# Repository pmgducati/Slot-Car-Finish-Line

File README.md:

# Slot Car Finish Line
 Pole Position Tower and Finsh line for Artin Slot Car Race Track

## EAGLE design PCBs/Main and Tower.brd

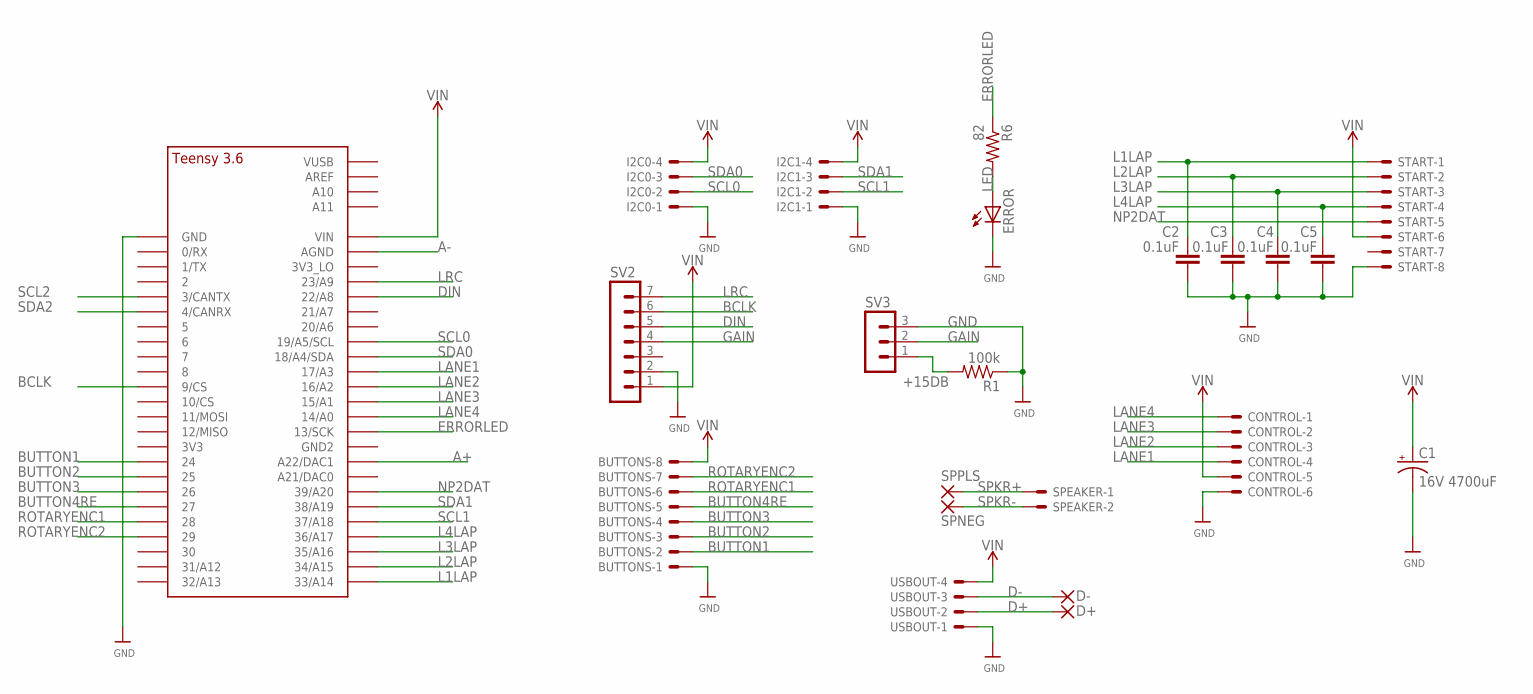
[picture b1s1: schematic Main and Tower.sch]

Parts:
BUTTONS: KK-156-8
C1: 16V 4700uF; CAPPRD550W110D1250H2500B
C2, C3, C4, C5: 0.1uF; CAPC3216X135
CONTROL: KK-156-6
D+: 1,6/0,8
D-: 1,6/0,8
ERROR: LEDCHIPLED_1206; CHIPLED_1206
I2C0, I2C1: KK-156-4
R1: 100k; M1206
R6: 82; M1206
SPEAKER: KK-156-2
SPNEG: 2,54/1,1
SPPLS: 2,54/1,1
START: KK-156-8
SV2: MA07-1
SV3: MA03-1
U$1: TEENSY_3.5/3.6_BASIC
USBOUT: KK-156-4

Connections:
+15DB: R1.2, SV3.1
A+: U$1.A22/DAC1
A-: U$1.AGND
BCLK: SV2.6, U$1.9/CS
BUTTON1: BUTTONS.2, U$1.24
BUTTON2: BUTTONS.3, U$1.25
BUTTON3: BUTTONS.4, U$1.26
BUTTON4RE: BUTTONS.5, U$1.27
D+: D+.1, USBOUT.2
D-: D-.1, USBOUT.3
DIN: SV2.5, U$1.22/A8
ERRORLED: R6.1, U$1.13/SCK
GAIN: SV2.4, SV3.2
GND: BUTTONS.1, C1.2 (-), C2.2, C3.2, C4.2, C5.2, CONTROL.6, ERROR.C, I2C0.1, I2C1.1, R1.1, START.8, SV2.2, SV3.3, U$1.GND, USBOUT.1
L1LAP: C2.1, START.1, U$1.33/A14
L2LAP: C3.1, START.2, U$1.34/A15
L3LAP: C4.1, START.3, U$1.35/A16
L4LAP: C5.1, START.4, U$1.36/A17
LANE1: CONTROL.4, U$1.17/A3
LANE2: CONTROL.3, U$1.16/A2
LANE3: CONTROL.2, U$1.15/A1
LANE4: CONTROL.1, U$1.14/A0
LED: ERROR.A, R6.2
LRC: SV2.7, U$1.23/A9
NP2DAT: START.5, U$1.39/A20
ROTARYENC1: BUTTONS.6, U$1.28
ROTARYENC2: BUTTONS.7, U$1.29
SCL0: I2C0.2, U$1.19/A5/SCL
SCL1: I2C1.2, U$1.37/A18
SCL2: U$1.3/CANTX
SDA0: I2C0.3, U$1.18/A4/SDA
SDA1: I2C1.3, U$1.38/A19
SDA2: U$1.4/CANRX
SPKR+: SPEAKER.1, SPPLS.1
SPKR-: SPEAKER.2, SPNEG.1
VIN: BUTTONS.8, C1.1 (+), CONTROL.5, I2C0.4, I2C1.4, START.6, SV2.1, U$1.VIN, USBOUT.4

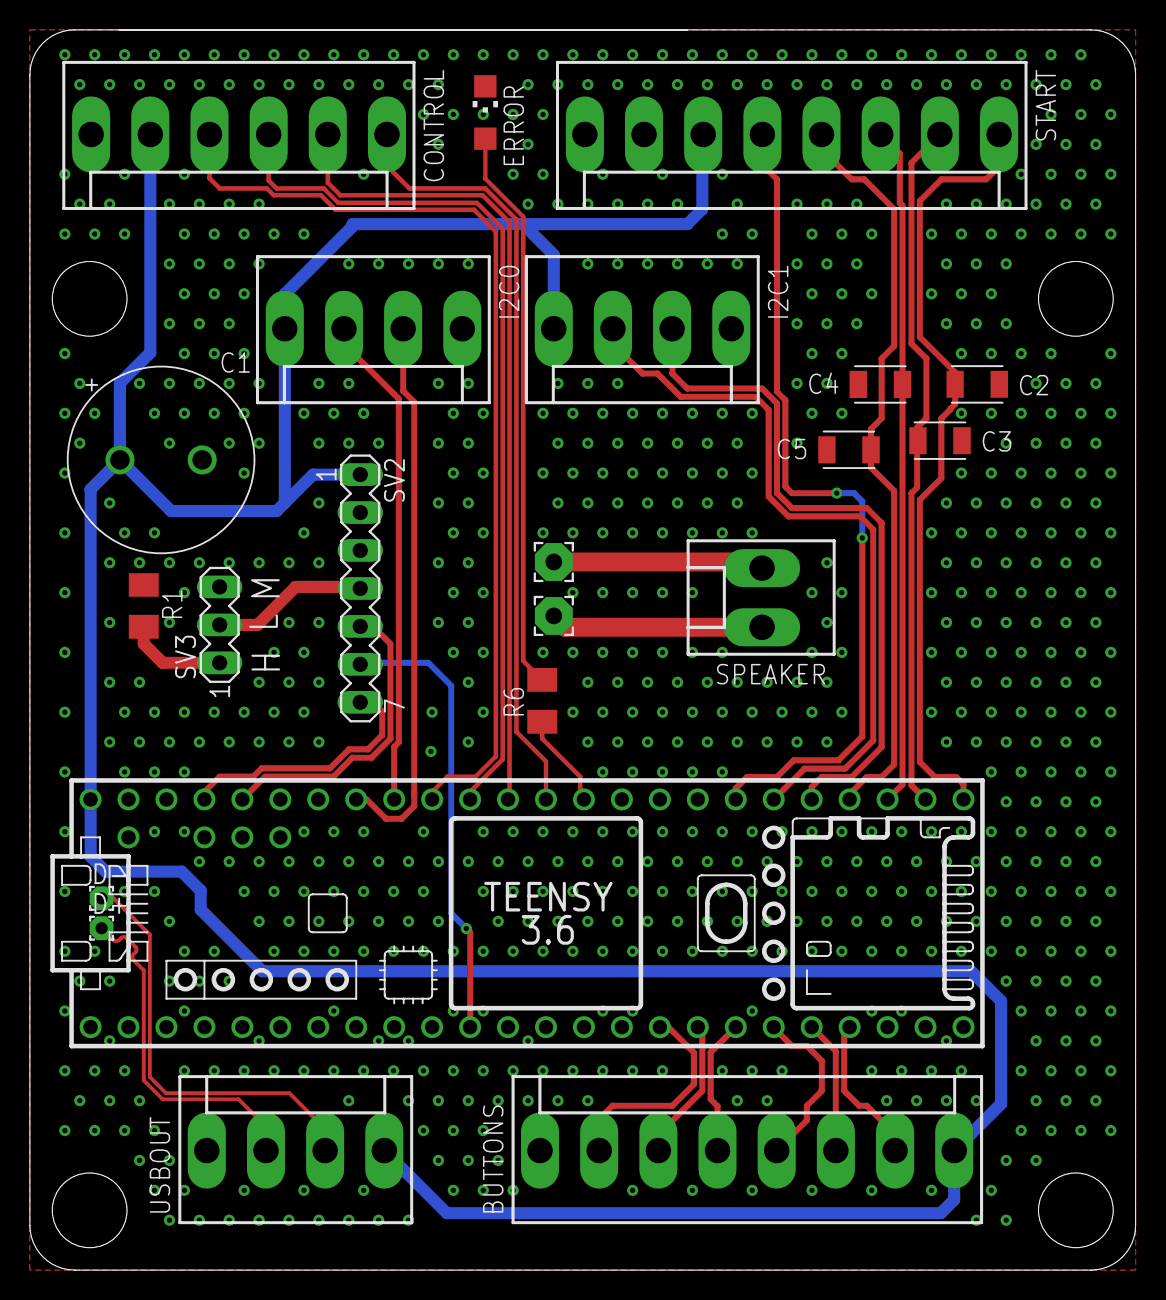
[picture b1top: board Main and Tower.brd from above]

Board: 2 copper layers, 74.0 x 83.0 mm, 22 parts (0 on the bottom side), 32 nets.

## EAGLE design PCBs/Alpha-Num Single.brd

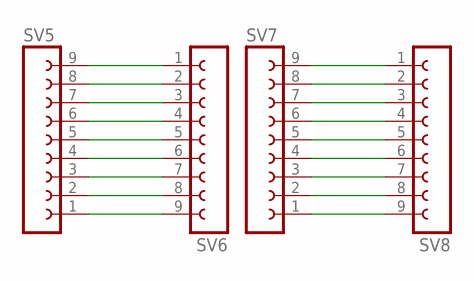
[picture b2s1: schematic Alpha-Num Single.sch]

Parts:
SV5, SV6, SV7, SV8: FE09-1; FE09

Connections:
unnamed: SV5.9, SV6.1
unnamed: SV5.8, SV6.2
unnamed: SV5.7, SV6.3
unnamed: SV5.6, SV6.4
unnamed: SV5.5, SV6.5
unnamed: SV5.4, SV6.6
unnamed: SV5.3, SV6.7
unnamed: SV5.2, SV6.8
unnamed: SV5.1, SV6.9
unnamed: SV7.9, SV8.1
unnamed: SV7.8, SV8.2
unnamed: SV7.7, SV8.3
unnamed: SV7.6, SV8.4
unnamed: SV7.5, SV8.5
unnamed: SV7.4, SV8.6
unnamed: SV7.3, SV8.7
unnamed: SV7.2, SV8.8
unnamed: SV7.1, SV8.9

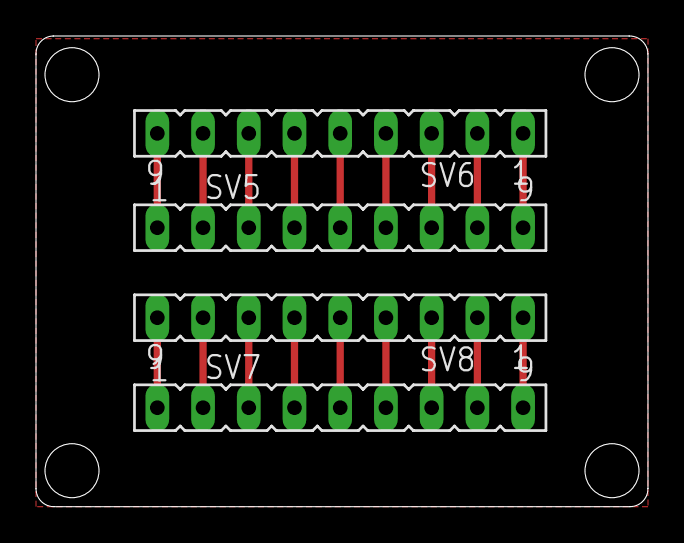
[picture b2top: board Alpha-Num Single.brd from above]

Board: 2 copper layers, 34.0 x 26.1 mm, 4 parts (0 on the bottom side), 18 nets.

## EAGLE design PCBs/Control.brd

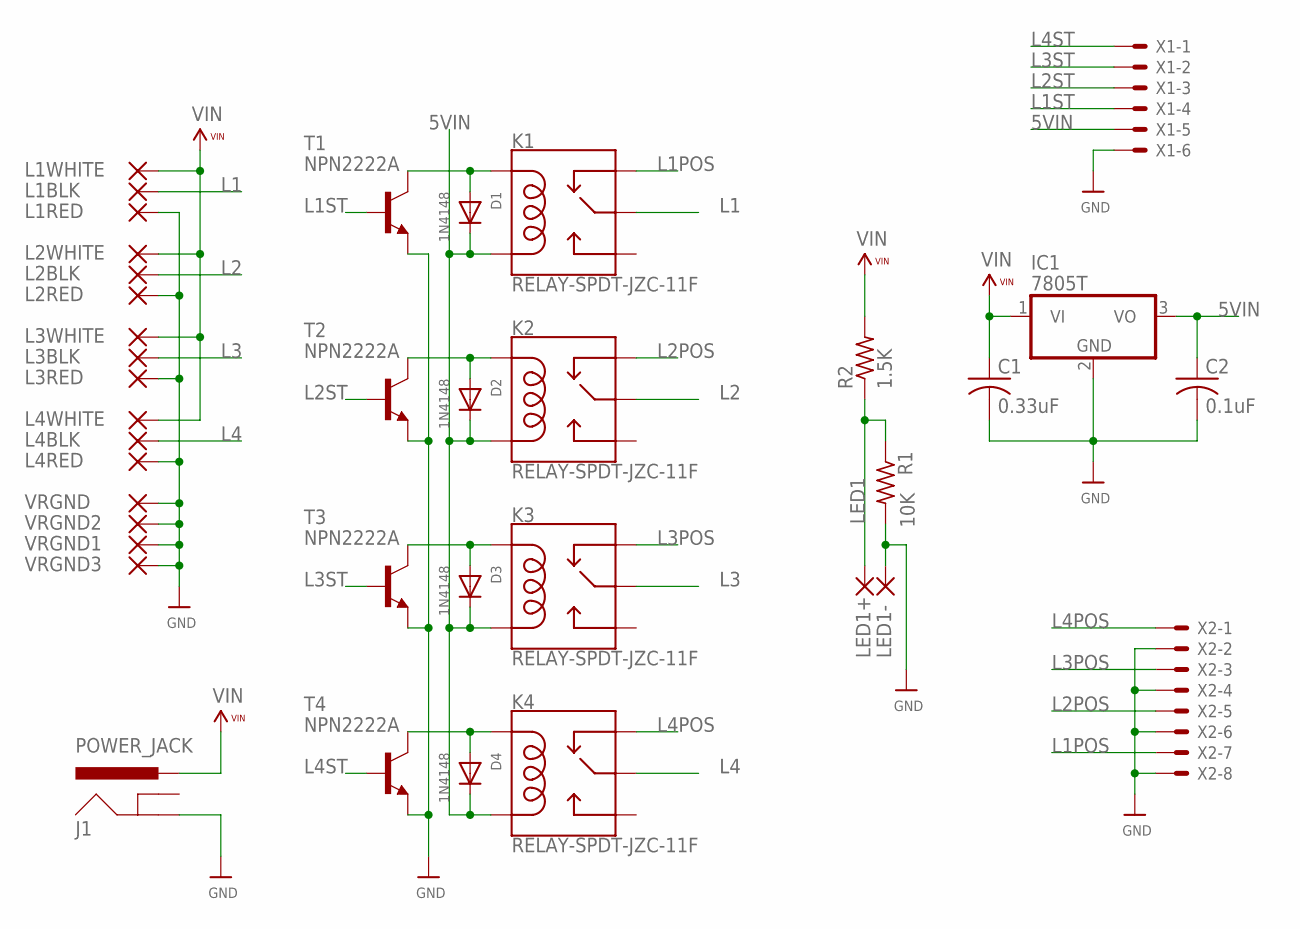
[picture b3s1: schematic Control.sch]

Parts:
C1: 0.33uF; C1206
C2: 0.1uF; C1206
D1, D2, D3, D4: 1N4148; DO-1N4148
IC1: 7805T; TO220H
J1: POWER_JACK; POWER_JACK_PTH
K1, K2, K3, K4: RELAY-SPDT-JZC-11F; RELAY-JZC
L1BLK, L1RED, L1WHITE, L2BLK, L2RED, L2WHITE, L3BLK, L3RED, L3WHITE, L4BLK, L4RED, L4WHITE: SMD5; SMD5,5X5
LED1+, LED1-: SMD5; SMD2,54-5,08
R1: 10K; M1206
R2: 1.5K; M1206
T1, T2, T3, T4: NPN2222A; TO92
VRGND, VRGND1, VRGND2, VRGND3: SMD5; SMD5,5X5
X1: KK-156-6
X2: KK-156-8

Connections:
5VIN: C2.1, D1.C, D2.C, D3.C, D4.C, IC1.3 (VO), K1.1 (COIL2), K2.1 (COIL2), K3.1 (COIL2), K4.1 (COIL2), X1.5
GND: C1.2, C2.2, IC1.2 (GND), J1.GND, L1RED.1, L2RED.1, L3RED.1, L4RED.1, LED1-.1, R1.2, T1.3 (E), T2.3 (E), T3.3 (E), T4.3 (E), VRGND.1, VRGND1.1, VRGND2.1, VRGND3.1, X1.6, X2.2, X2.4, X2.6, X2.8
L1: K1.4 (MAIN), L1BLK.1
L1POS: K1.2 (NC), X2.7
L1ST: T1.2 (B), X1.4
L2: K2.4 (MAIN), L2BLK.1
L2POS: K2.2 (NC), X2.5
L2ST: T2.2 (B), X1.3
L3: K3.4 (MAIN), L3BLK.1
L3POS: K3.2 (NC), X2.3
L3ST: T3.2 (B), X1.2
L4: K4.4 (MAIN), L4BLK.1
L4POS: K4.2 (NC), X2.1
L4ST: T4.2 (B), X1.1
LED1: LED1+.1, R1.1, R2.1
unnamed: D2.A, K2.5 (COIL1), T2.1 (C)
unnamed: D1.A, K1.5 (COIL1), T1.1 (C)
unnamed: D3.A, K3.5 (COIL1), T3.1 (C)
unnamed: D4.A, K4.5 (COIL1), T4.1 (C)
VIN: C1.1, IC1.1 (VI), J1.PWR, L1WHITE.1, L2WHITE.1, L3WHITE.1, L4WHITE.1, R2.2

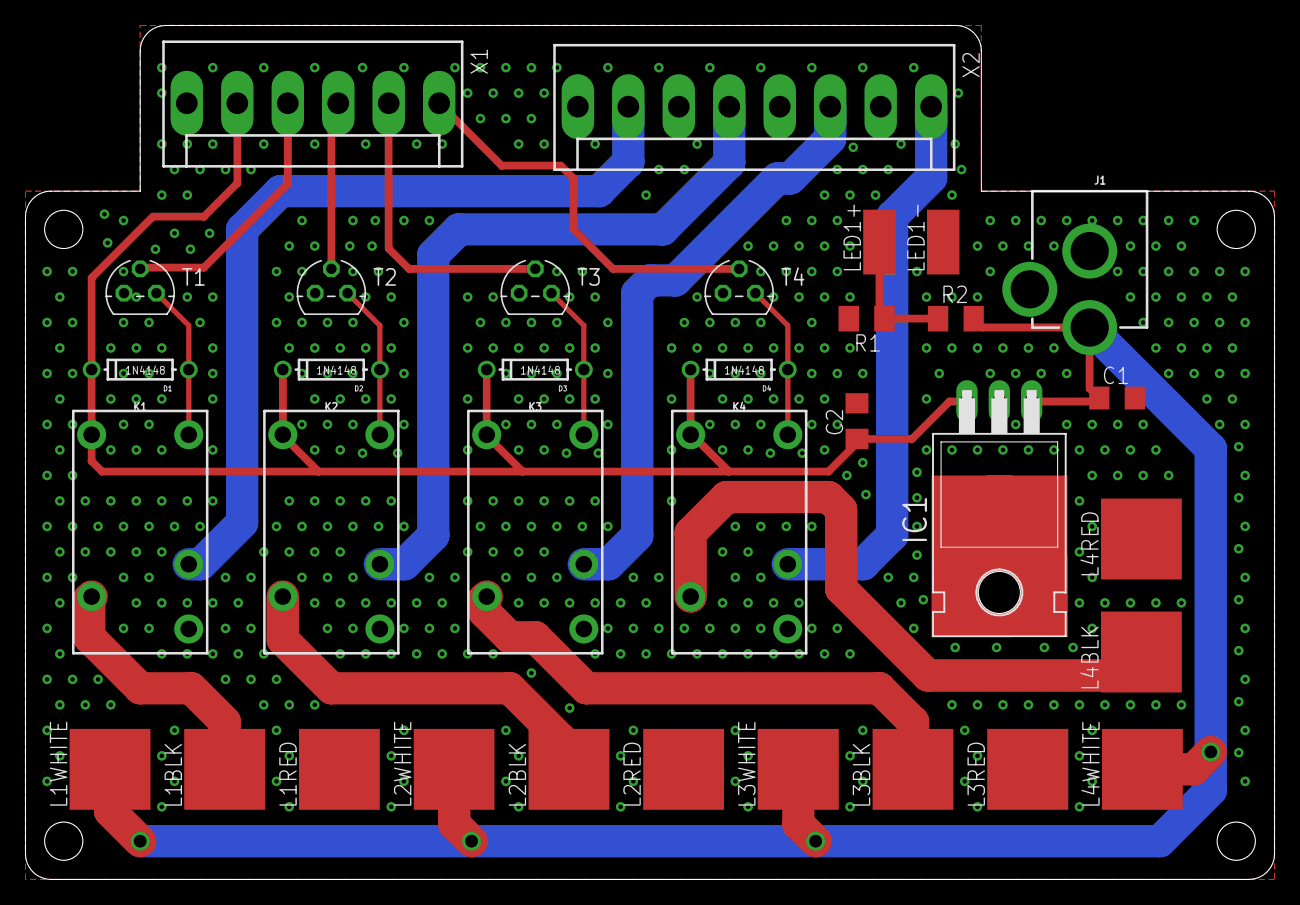
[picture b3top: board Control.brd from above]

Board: 2 copper layers, 98.0 x 67.0 mm, 38 parts (0 on the bottom side), 20 nets.

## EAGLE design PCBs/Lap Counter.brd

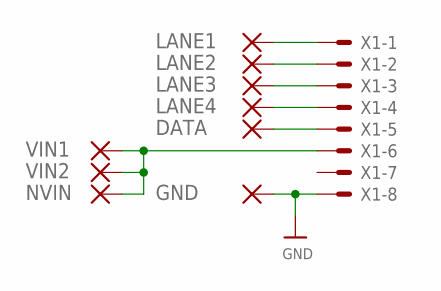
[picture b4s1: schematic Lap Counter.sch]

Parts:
DATA: SMD5; SMD2,54-5,08
GND: SMD5; SMD2,54-5,08
LANE1, LANE2, LANE3, LANE4: SMD5; SMD2,54-5,08
NVIN: SMD5; SMD2,54-5,08
VIN1, VIN2: SMD5; SMD2,54-5,08
X1: KK-156-8

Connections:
DATA: DATA.1, X1.5
GND: GND.1, X1.8
LANE1: LANE1.1, X1.1
LANE2: LANE2.1, X1.2
LANE3: LANE3.1, X1.3
LANE4: LANE4.1, X1.4
VIN: NVIN.1, VIN1.1, VIN2.1, X1.6

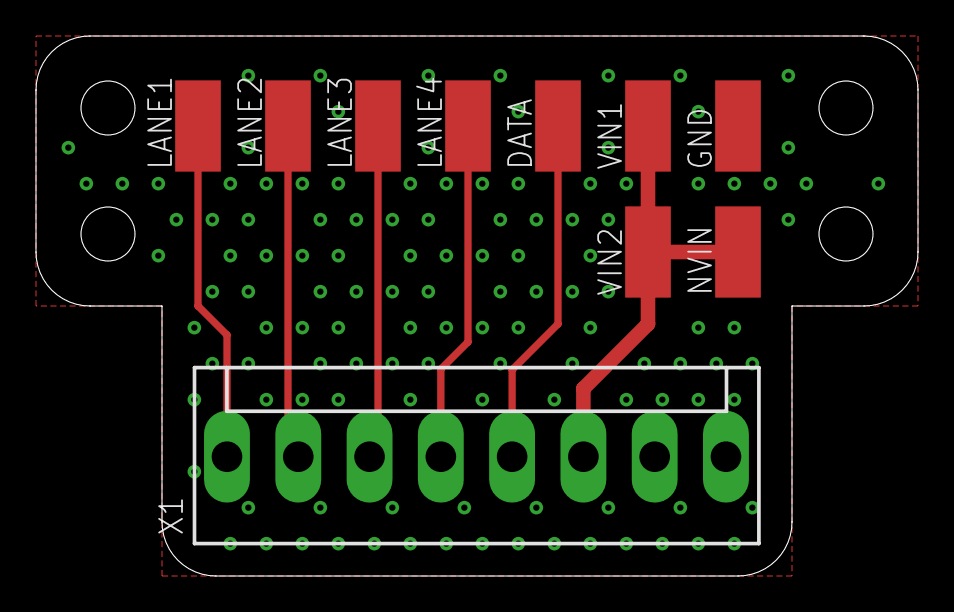
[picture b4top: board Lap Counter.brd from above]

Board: 2 copper layers, 49.0 x 30.0 mm, 10 parts (0 on the bottom side), 7 nets.

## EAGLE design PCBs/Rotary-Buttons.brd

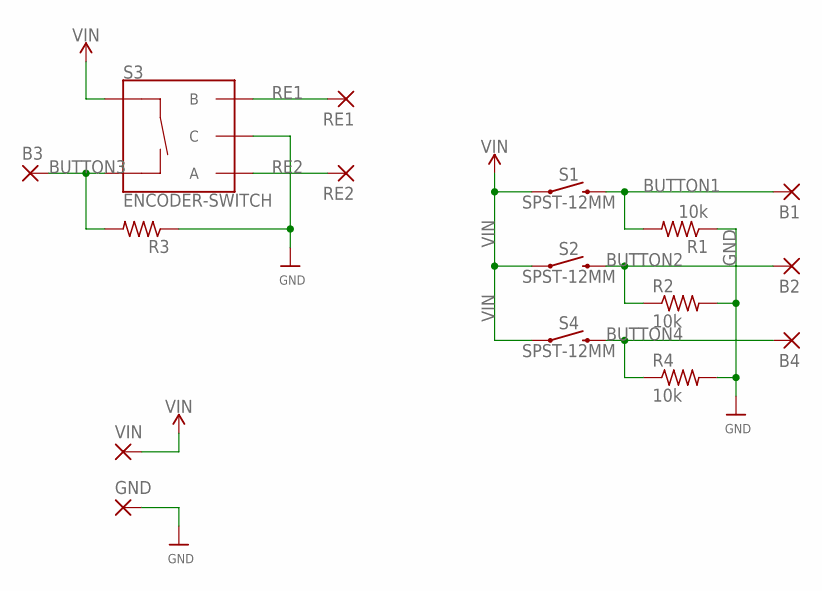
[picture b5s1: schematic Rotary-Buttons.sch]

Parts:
B1, B2, B3, B4: SMD5; SMD2,54-5,08
GND: SMD5; SMD2,54-5,08
R1, R2, R4: 10k; R1206
R3: R-US_R1206; R1206
RE1, RE2: SMD5; SMD2,54-5,08
S1, S2, S4: SPST-12MM; TACTILE_SWITCH_PTH_12MM
S3: ENCODER-SWITCH; ROTARY_ENC_PLAIN
VIN: SMD5; SMD2,54-5,08

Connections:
BUTTON1: B1.1, R1.2, S1.3 (2)
BUTTON2: B2.1, R2.1, S2.3 (2)
BUTTON3: B3.1, R3.2, S3.SW-
BUTTON4: B4.1, R4.1, S4.3 (2)
GND: GND.1, R1.1, R2.2, R3.1, R4.2, S3.C
RE1: RE1.1, S3.B
RE2: RE2.1, S3.A
VIN: S1.1, S2.1, S3.SW+, S4.1, VIN.1

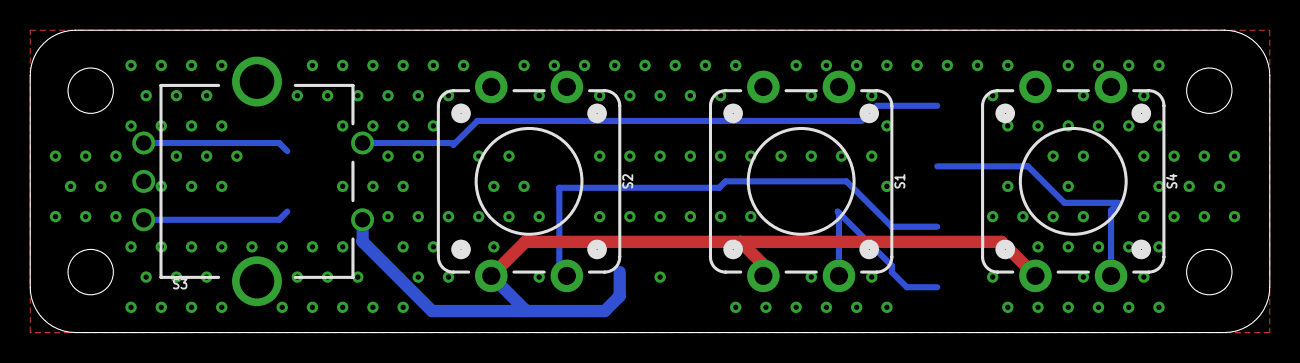
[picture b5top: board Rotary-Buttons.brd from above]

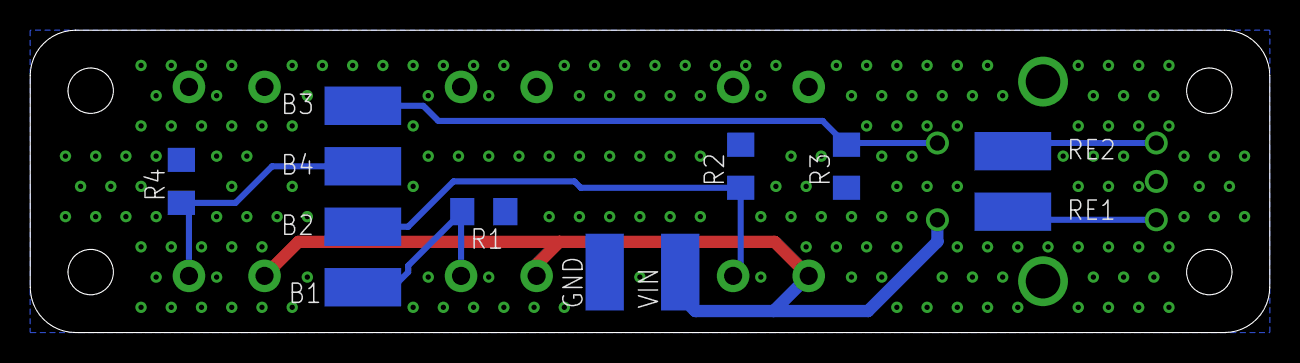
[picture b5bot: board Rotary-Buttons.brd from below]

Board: 2 copper layers, 82.0 x 20.0 mm, 16 parts (12 on the bottom side), 8 nets.

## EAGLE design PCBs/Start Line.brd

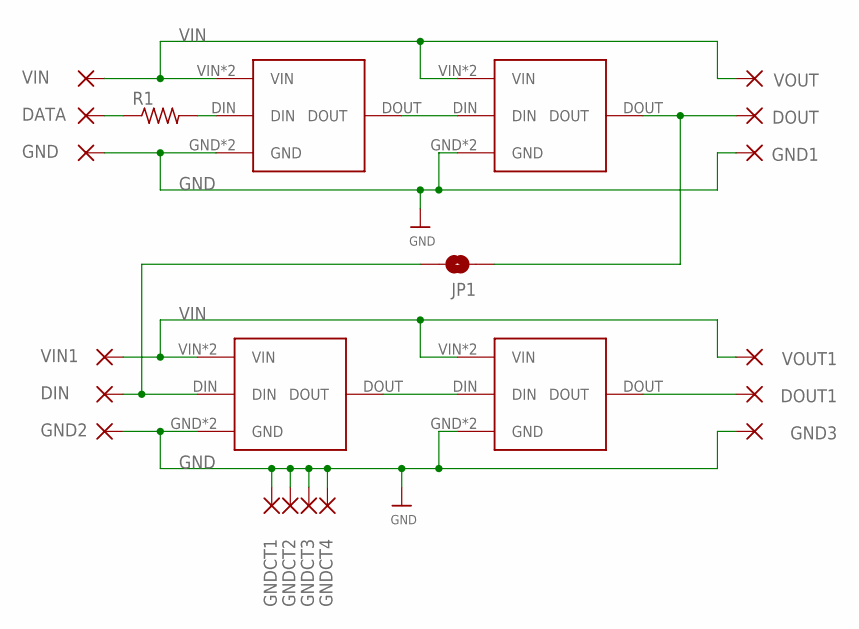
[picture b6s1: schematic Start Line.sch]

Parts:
DATA: SMD5; SMD2,54-5,08
DIN: SMD5; SMD2,54-5,08
DOUT, DOUT1: SMD5; SMD2,54-5,08
GND, GND1, GND2, GND3: SMD5; SMD2,54-5,08
GNDCT1, GNDCT2, GNDCT3, GNDCT4: SMD5; SMD5,5X5
JP1: JUMPER-SMT_2_NO_SILK; SMT-JUMPER_2_NO_SILK
R1: R-US_R1206; R1206
U$1, U$3: NP-1
U$5, U$8: NP-3
VIN, VIN1: SMD5; SMD2,54-5,08
VOUT, VOUT1: SMD5; SMD2,54-5,08

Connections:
DATA: DATA.1, R1.1
DIN1: R1.2, U$5.DIN
DIN2: U$5.DOUT, U$8.DIN
DIN3: DIN.1, JP1.2, U$1.DIN
DIN4: U$1.DOUT, U$3.DIN
DOUT: DOUT.1, JP1.1, U$8.DOUT
DOUT1: DOUT1.1, U$3.DOUT
GND: GND.1, GND1.1, GND2.1, GND3.1, GNDCT1.1, GNDCT2.1, GNDCT3.1, GNDCT4.1, U$1.GND, U$1.GND1 (GND), U$3.GND, U$3.GND1 (GND), U$5.GND, U$5.GND1 (GND), U$8.GND, U$8.GND1 (GND)
VIN: U$1.VIN, U$1.VOUT (VIN), U$3.VIN, U$3.VOUT (VIN), U$5.VIN, U$5.VOUT (VIN), U$8.VIN, U$8.VOUT (VIN), VIN.1, VIN1.1, VOUT.1, VOUT1.1

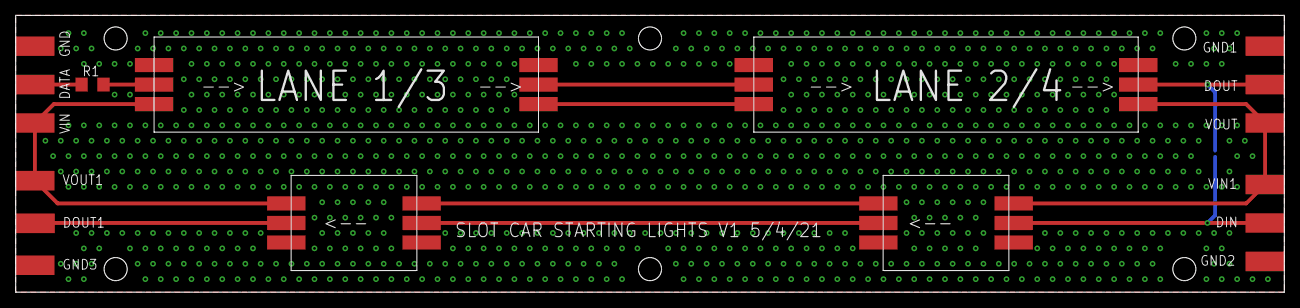
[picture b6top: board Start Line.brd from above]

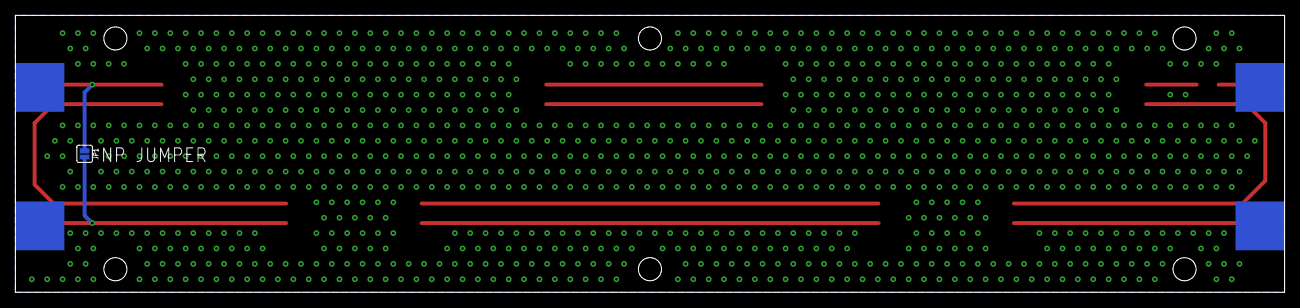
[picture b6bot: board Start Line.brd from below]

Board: 2 copper layers, 165.0 x 36.0 mm, 22 parts (5 on the bottom side), 9 nets.

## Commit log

2022-03-23 Initial File Commit
    Last repository Creation....
2023-02-16 Library Add
2023-02-16 Updating Libraries for progress
    I managed to solved 20 of the 23 errors in the LED backpack library. Working on the last 3
2023-08-28 update
    update
2023-10-28 Features
    Features added:
    Leaderboard lap times and Record
    Persistent Lap Record Car and Time
    Overall Code Clean Up
    EEPROM Erase Option in Main Menu
    Removed:
2024-01-11 ROB CODE REVIEW
2024-02-09 V1.0
    Sort is working correctly
    Finish line LEDs are reporting the correct finish order
    Lap counter displays "FL" at last lap through finish (was counting beyond specified number of Laps)
    Finished Less then 4 racers functionality:
    Finish Line LEDs and Leaderboard entries are blank for unused lanes
    Fixed issue where Lane 1 and Lane 2 time was swapped.
2024-02-13 Lan Unique Actions
    This addresses Issues #3 and #1
2024-02-13 New Features
    Resolved Issues 1,2,3,8,10
2024-02-13 cleanup
2024-02-14 Added Options Menu
    Option Menu includes the ability to set the End Race delay, Penalty delay and Track Debounce time and commit to EEPROM. The erase Lap record was moved from the main flow to the options menu. To Acces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
2024-02-14 Working on Code Cleanup
    All Console Prints have been removed, Comments updated/added.
    To do: Standardize Variable Names
2024-02-20 Issues #6 and #9
    This Addresses Issues #6 and #9
    Code Changes:
    1. Relay Pin order had to be reversed
    2. Record_Lap and lap_time changed from unsigned short to unsigned long
    3. Penalty_LaneX (1-4) changed from 0 to 1 to work with change to PULLUP on Lap Pins
    4. Changed pinmode for LANEXLAP (1-4) from INPUT to INPUT_PULLUP
2024-02-21 Standardized All Variable Naems
2024-03-05 Swap p1time and p2time variables
2024-03-05 Move the sort function to be part of the leaderboard display function
2024-03-09 Fix comment type-o
2024-03-09 Update Car_Num_Lane_Assign function
2024-03-09 Remove unused variable
2024-03-09 Update Options function
2024-03-09 Update qsort helper functions descriptions
2024-03-09 Minor updates to Menu_Debounce_Track
2024-03-09 Minor updates to Menu_Penalty
2024-03-09 Minor updates to Menu_Stop_Race
2024-03-09 Minor updates to Number_of_Racers
2024-03-13 Minor updates to Number_of_Laps
2024-03-13 Update comment spacing
2024-03-13 Minor updates to Clear_Record_Lap
2024-03-14 Comment spacing updates
2024-03-14 Make Screen_Rotary_Update a local variable so we don't have to always reset it
2024-03-14 Fix bad if statement
2024-03-14 Add some spacing for readability
2024-03-17 Resolve compile time warnings from alpa num display conversions
2024-03-20 Convert player Adafruit_AlphaNum4 variables to arrays and leaderboard displays to loops
2024-03-23 Add last lap to the car struct
2024-03-25 Convert lanes to structs and convert repeat if statements to loops
2024-03-27 Small updates and bug fixes
2024-03-27 Implement lane selection during car number assignment
2024-03-28 Car loop array index bug fix
2024-03-28 Minor syntax tweaks
2024-04-01 Rename read button functions
2024-04-28 Prevent repeated LOW lane states from triggering another lap count
2024-04-28 Fix the spellings of penalty
2025-10-10 Redesign the menu structure and begin redesign
2025-10-12 Continue refactoring with race states
2025-10-12 Continue cleanup
2025-10-12 More variable and function cleanup
2025-10-12 Continue refactoring
2025-10-12 More refactor work
2025-11-23 Minor variable updates
2026-04-30 Fix displaying Player_PolePositions
2026-04-30 Update Display_Leaderboard to show decimal places based on length of lap time
2026-04-30 Add ability to show details of a configured car during setup
2026-04-30 Add displaying an asterisk for already configured cars
2026-04-30 Add ability to initialize 1 car or lane at a time or all cars or lanes at once
2026-04-30 Fix debounce on rotary encoder reads
2026-04-30 Add required function prototypes
2026-04-30 Fix Player_Times addresses
2026-04-30 Update how record laps are recorded and displayed
2026-04-30 Remove magic numbers from Option_Clear_Record_Lap
2026-04-30 Improve backing out of options menus
2026-04-30 Add displaying which car is being configured for a selected lane
2026-04-30 Reset a car and lane if reconfiguring an already configured car
2026-04-30 Add ability to stop a paused race
2026-04-30 Improve Clear_Race steps
2026-04-30 Improve race timings for start time, pause durations, lap time, total time, and penalty time
2026-05-06 Improve menuing
2026-05-06 Display total race time at race end
2026-05-06 Try to ensure serial output is ready
2026-05-06 Update some Num_Lanes and Num_Racers references
2026-05-07 Update function names
2026-05-09 Update function and variable names to be consistent
2026-05-09 Add some function descriptions
2026-05-09 Remove unneeded penaltyStartTime

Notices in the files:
parts and their libraries:
SparkFun-Connectors: Licensing: Creative Commons ShareAlike 4.0 International - https://creativecommons.org/licenses/by-sa/4.0
PatternAgents-Beautify: License : http://creativecommons.org/licenses/by-sa/3.0
(Creative Commons 3.0)
